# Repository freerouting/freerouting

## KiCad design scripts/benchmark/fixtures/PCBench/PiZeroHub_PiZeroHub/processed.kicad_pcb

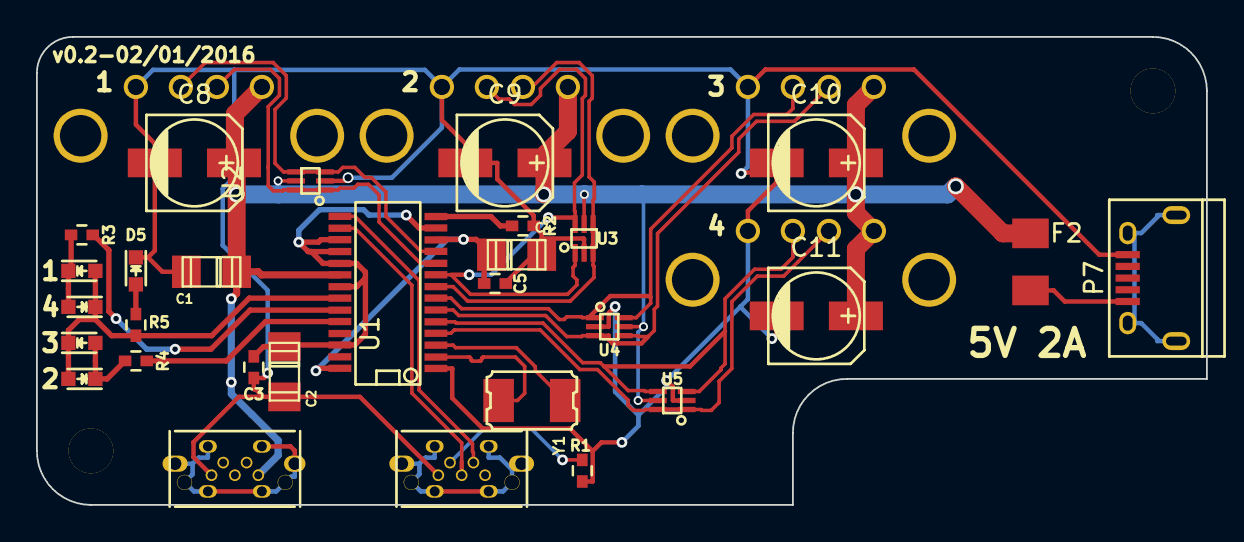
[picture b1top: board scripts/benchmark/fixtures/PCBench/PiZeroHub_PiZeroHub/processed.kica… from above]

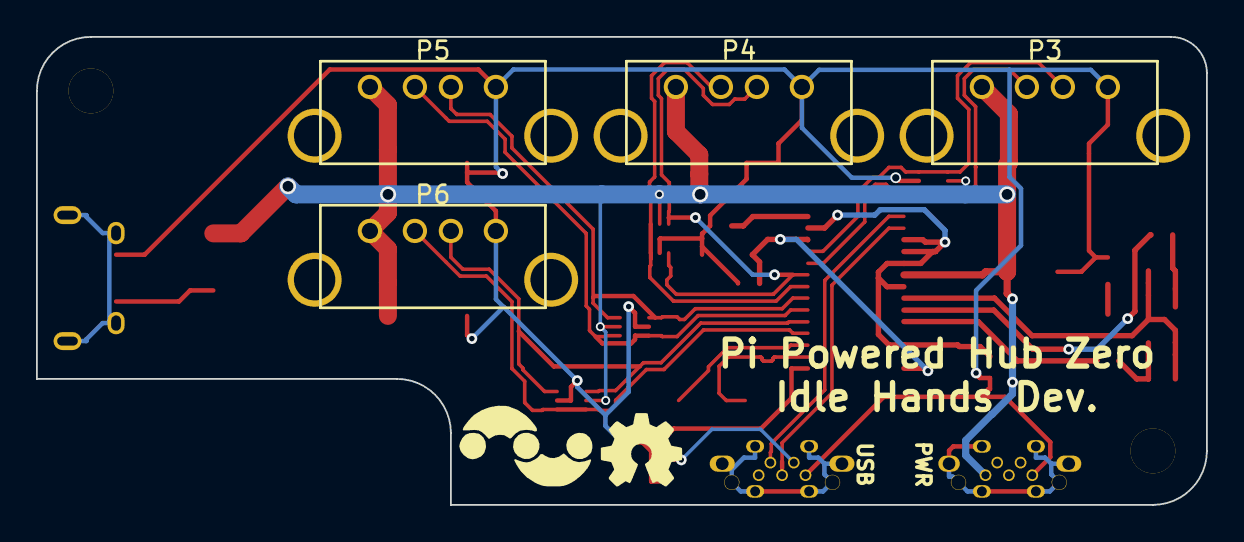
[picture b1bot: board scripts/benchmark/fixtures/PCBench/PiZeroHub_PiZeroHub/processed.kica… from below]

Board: 2 copper layers, 65.0 x 26.0 mm, 33 parts (4 on the bottom side), 25 nets.

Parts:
C1, C2, C4: 10uF; c_1206_pol
C3, C5: 0.1uF; C_0402_Hand
C8, C9, C10, C11: 100uF; c_elec_5x5.3
D1, D2, D3, D4: Green; LED-0603
D5: Red; LED-0603
F2: 2A; Fuse_SMD1206_Wave
P1, P2: USB_OTG; USBOTG_BoardMount
P3, P4, P5, P6: USB_B; USB_A_Vert
P7: USB_POWER; USB_Micro-B
R1: 100k; R_0402_Hand
R2: 2.7k; R_0402_Hand
R3, R4, R5: 1k; R_0402_Hand
U1: FE1_1_4PORTUSB; SSOT28
U2, U3, U4, U5: USBLC6-2; SOT-666
Y1: Crystal_Small; crystal_smd_5x3.2mm

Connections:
+3V3: C2.1, C3.1, U1.13, U1.17, U1.18, U1.19, U1.21, U1.26
+5V: C1.1, C8.1, C9.1, C10.1, C11.1, F2.2, P1.1, P3.1, P4.1, P5.1, P6.1, U1.20, U2.5, U3.5, U4.5, U5.5
/D1+: P3.3, U1.11, U2.3, U2.4
/D1-: P3.2, U1.10, U2.1, U2.6
/D2+: P4.3, U1.9, U3.1, U3.6
/D2-: P4.2, U1.8, U3.3, U3.4
/D3+: P5.3, U1.7, U4.1, U4.6
/D3-: P5.2, U1.6, U4.3, U4.4
/D4+: P6.3, U1.5, U5.3, U5.4
/D4-: P6.2, U1.4, U5.1, U5.6
/X+: U1.3, Y1.2
/X-: U1.2, Y1.1
GND: C1.2, C2.2, C3.2, C4.2, C5.2, C8.2, C9.2, C10.2, C11.2, D5.1, P1.5, P2.5, P3.4, P4.4, P5.4, P6.4, P7.5, R1.1, R2.2, U1.1, U2.2, U3.2, U4.2, U5.2
unnamed: C4.1, C5.1, U1.12, U1.28
unnamed: D1.1, D2.2, R3.1
unnamed: D1.2, D2.1, D3.1, D4.2, R5.2, U1.22
unnamed: D3.2, D4.1, R4.1
unnamed: D5.2, R5.1
unnamed: F2.1, P7.1
unnamed: P2.2, U1.15
unnamed: P2.3, U1.16
unnamed: P2.4, R1.2
unnamed: R2.1, U1.14
unnamed: R3.2, U1.23
unnamed: R4.2, U1.24

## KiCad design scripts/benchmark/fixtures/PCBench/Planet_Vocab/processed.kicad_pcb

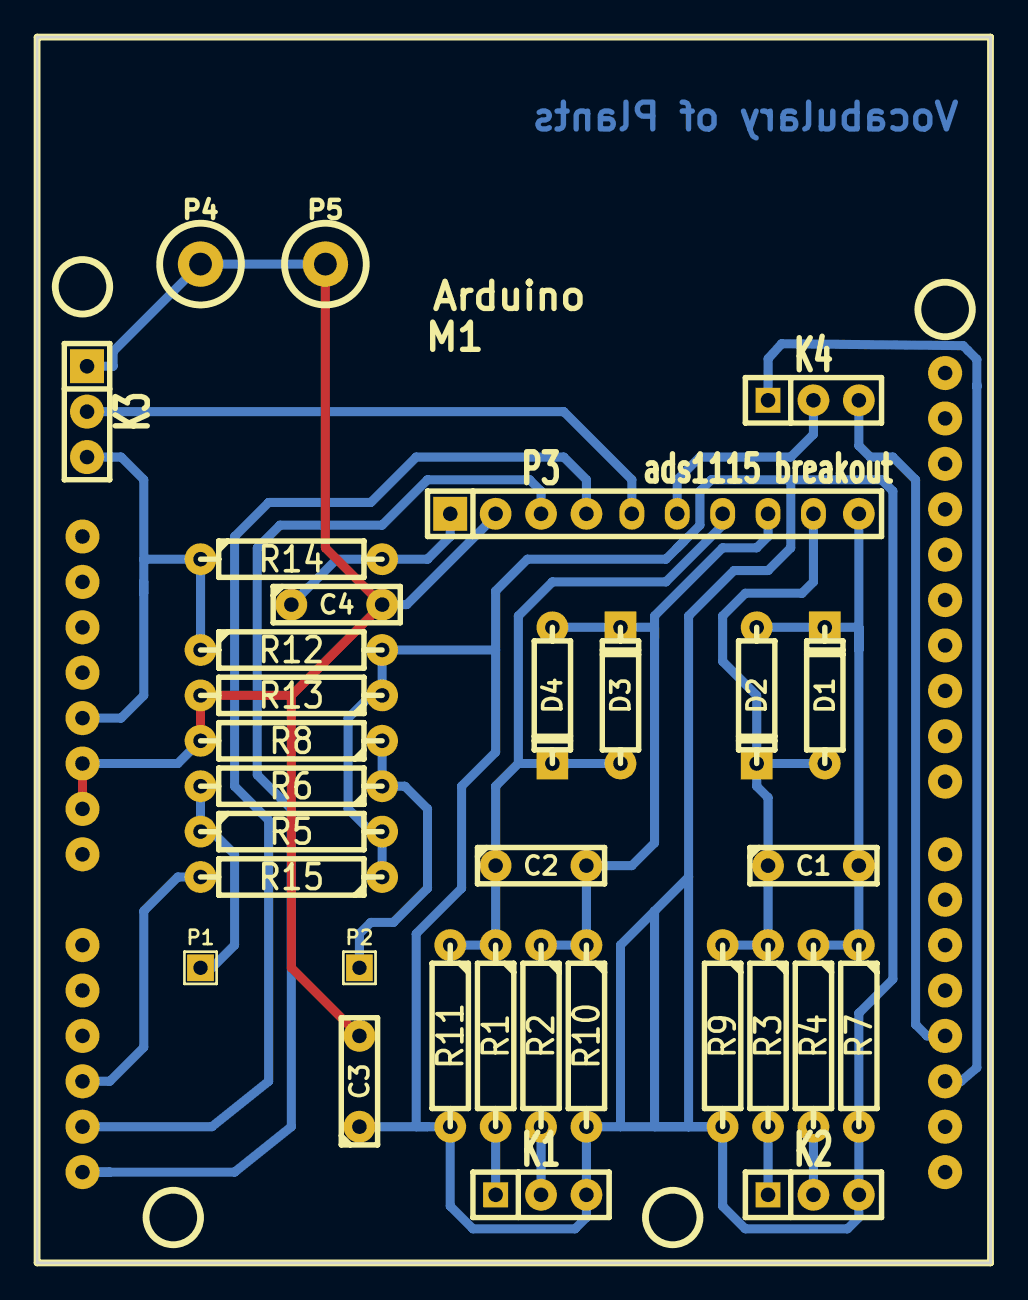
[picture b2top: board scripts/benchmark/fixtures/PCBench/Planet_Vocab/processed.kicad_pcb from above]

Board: 2 copper layers, 53.3 x 68.6 mm, 33 parts (0 on the bottom side), 21 nets.

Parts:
C1, C2: 100n; C2
C3, C4: 10u; C2
D1, D2, D3, D4: 1n914; D3
K1, K2, K3, K4: CONN_3; SIL-3
M1: Arduino
P1, P2: CONN_1; SIL-1
P3: ads1115 breakout; SIL-10
P4, P5: CONN_1; 1pin
R1, R2, R3, R4: 100K; R4-LARGE_PADS
R5, R12, R13, R15: 10k; R4-LARGE_PADS
R6: 100k; R4-LARGE_PADS
R7, R8, R9, R10, R11: 1M; R4-LARGE_PADS
R14: 0R; R4-LARGE_PADS

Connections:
+5V: K3.3, M1.3, R12.1, R14.1
GND: C3.2, C4.2, K3.1, M1.4, M1.5, P3.2, P4.1, P5.1, R8.2, R13.2
unnamed: C2.1, D3.1, D4.2, P3.7, R1.1, R11.1
unnamed: M1.12, P3.3
unnamed: M1.11, P3.4
unnamed: C4.1, P3.1, R14.2
unnamed: M1.10, R15.2
unnamed: K4.2, P3.6
unnamed: P2.1, R6.1, R8.1
unnamed: P1.1, R5.1, R6.2
unnamed: K4.1, M1.15
unnamed: K4.3, M1.16
unnamed: K3.2, P3.5
unnamed: C2.2, D3.2, D4.1, P3.8, R2.1, R10.1
unnamed: K1.1, R1.2
unnamed: K1.2, R2.2
unnamed: K2.1, R3.2
unnamed: K2.2, R4.2
unnamed: C3.1, K1.3, K2.3, R5.2, R7.2, R9.2, R10.2, R11.2, R12.2, R13.1, R15.1
unnamed: C1.1, D1.1, D2.2, P3.9, R3.1, R9.1
unnamed: C1.2, D1.2, D2.1, P3.10, R4.1, R7.1
